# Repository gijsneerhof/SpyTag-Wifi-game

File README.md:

# WIFI Spy Tag game

Hey there, this is the code used for the WIFI based hide and seek/tag game using ESP8266 devices.
The idea behind the game is that humans go and hide, while two zombies (or agents) start seeking them out.
once a zombie comes in proximity to a human, they turn into zombies themselves. Eventually this game will
be rebranded to a spy type of game, with more powerups and features to play around with.

This project is currently in basic WIP shape, if you would like to burn and test out this project however,
more info can be found here for how to accomplish this: https://github.com/con-f-use/esp82XX-basic

## Hardware

Coming soon!

## Instructions

### Installation

Espressif IDF toolchain

### Usage

The function `user_init()` in `user/user_main.c` will be run first. 

### Building

First do `make erase`, then `make initdefault #init3v3` to set the flash correctly.
Lastly, use `make burn` to upload to the ESP8266 controller over `/dev/ttyUSB0`

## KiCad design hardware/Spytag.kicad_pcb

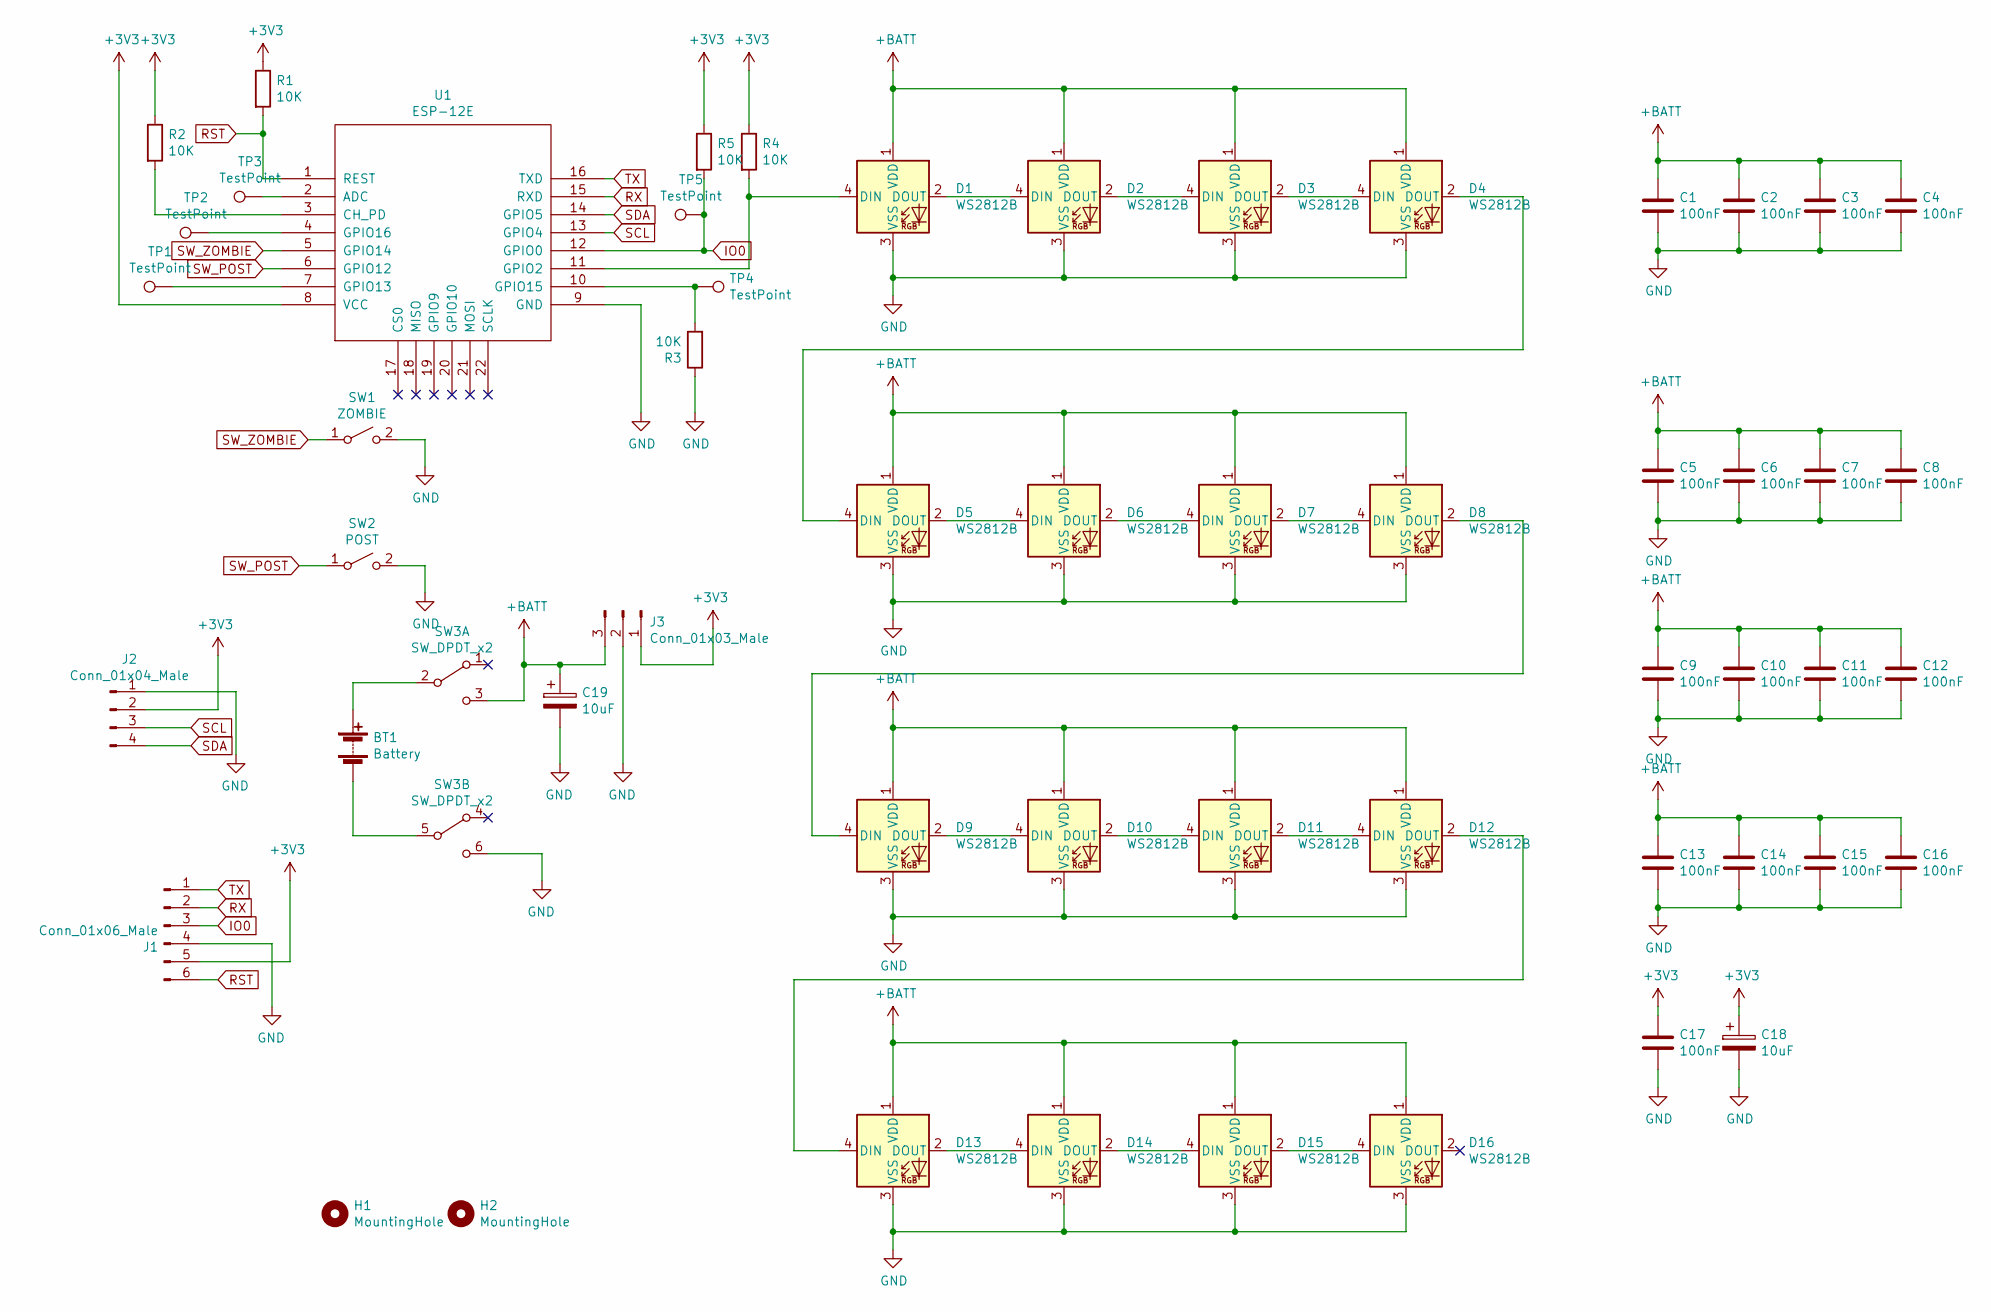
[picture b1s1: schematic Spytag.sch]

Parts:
BT1: Battery; Generic
C1, C2, C3, C4, C5, C6, C7, C8, C9, C10, C11, C12, C13, C14, C15, C16, C17: 100nF; C_0603_1608Metric
C18, C19: 10uF; C_0603_1608Metric
D1, D2, D3, D4, D5, D6, D7, D8, D9, D10, D11, D12, D13, D14, D15, D16: WS2812B; LED_WS2812B_PLCC4_5.0x5.0mm_P3.2mm
H1, H2: MountingHole; MountingHole_3.2mm_M3
J1: Conn_01x06_Male; PinHeader_1x06_P2.54mm_Vertical
J2: Conn_01x04_Male; PinHeader_1x04_P2.54mm_Vertical
J3: Conn_01x03_Male; PinSocket_1x03_P2.54mm_Vertical
R1, R2, R3, R4, R5: 10K; R_0603_1608Metric
SW1: ZOMBIE; SW_PUSH_6mm
SW2: POST; SW_PUSH_6mm
SW3: SW_DPDT_x2; SW_E-Switch_EG1271_DPDT
TP1, TP2, TP3, TP4, TP5: TestPoint; TestPoint_THTPad_D1.5mm_Drill0.7mm
U1: ESP-12E; ESP-12E_SMD

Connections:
+3V3: C17.1, C18.1, J1.5, J2.2, J3.1, R1.1, R2.1, R4.1, R5.1, U1.8 (VCC)
+BATT: C1.1, C2.1, C3.1, C4.1, C5.1, C6.1, C7.1, C8.1, C9.1, C10.1, C11.1, C12.1, C13.1, C14.1, C15.1, C16.1, C19.1, D1.1 (VDD), D2.1 (VDD), D3.1 (VDD), D4.1 (VDD), D5.1 (VDD), D6.1 (VDD), D7.1 (VDD), D8.1 (VDD), D9.1 (VDD), D10.1 (VDD), D11.1 (VDD), D12.1 (VDD), D13.1 (VDD), D14.1 (VDD), D15.1 (VDD), D16.1 (VDD), J3.3, SW3.3 (C)
GND: C1.2, C2.2, C3.2, C4.2, C5.2, C6.2, C7.2, C8.2, C9.2, C10.2, C11.2, C12.2, C13.2, C14.2, C15.2, C16.2, C17.2, C18.2, C19.2, D1.3 (VSS), D2.3 (VSS), D3.3 (VSS), D4.3 (VSS), D5.3 (VSS), D6.3 (VSS), D7.3 (VSS), D8.3 (VSS), D9.3 (VSS), D10.3 (VSS), D11.3 (VSS), D12.3 (VSS), D13.3 (VSS), D14.3 (VSS), D15.3 (VSS), D16.3 (VSS), J1.4, J2.1, J3.2, R3.1, SW1.2 (B), SW2.2 (B), SW3.6 (C), U1.9 (GND)
IO0: J1.3, R5.2, TP5.1, U1.12 (GPIO0)
unnamed: BT1.1 (+), SW3.2 (B)
unnamed: BT1.2 (-), SW3.5 (B)
unnamed: D1.2 (DOUT), D2.4 (DIN)
unnamed: D1.4 (DIN), R4.2, U1.11 (GPIO2)
unnamed: D2.2 (DOUT), D3.4 (DIN)
unnamed: D3.2 (DOUT), D4.4 (DIN)
unnamed: D4.2 (DOUT), D5.4 (DIN)
unnamed: D5.2 (DOUT), D6.4 (DIN)
unnamed: D6.2 (DOUT), D7.4 (DIN)
unnamed: D7.2 (DOUT), D8.4 (DIN)
unnamed: D8.2 (DOUT), D9.4 (DIN)
unnamed: D10.2 (DOUT), D11.4 (DIN)
unnamed: D9.2 (DOUT), D10.4 (DIN)
unnamed: D11.2 (DOUT), D12.4 (DIN)
unnamed: D12.2 (DOUT), D13.4 (DIN)
unnamed: D13.2 (DOUT), D14.4 (DIN)
unnamed: D14.2 (DOUT), D15.4 (DIN)
unnamed: D15.2 (DOUT), D16.4 (DIN)
unnamed: R2.2, U1.3 (CH_PD)
unnamed: R3.2, TP4.1, U1.10 (GPIO15)
unnamed: TP1.1, U1.7 (GPIO13)
unnamed: TP2.1, U1.4 (GPIO16)
unnamed: TP3.1, U1.2 (ADC)
RST: J1.6, R1.2, U1.1 (REST)
RX: J1.2, U1.15 (RXD)
SCL: J2.3, U1.13 (GPIO4)
SDA: J2.4, U1.14 (GPIO5)
SW_POST: SW2.1 (A), U1.6 (GPIO12)
SW_ZOMBIE: SW1.1 (A), U1.5 (GPIO14)
TX: J1.1, U1.16 (TXD)

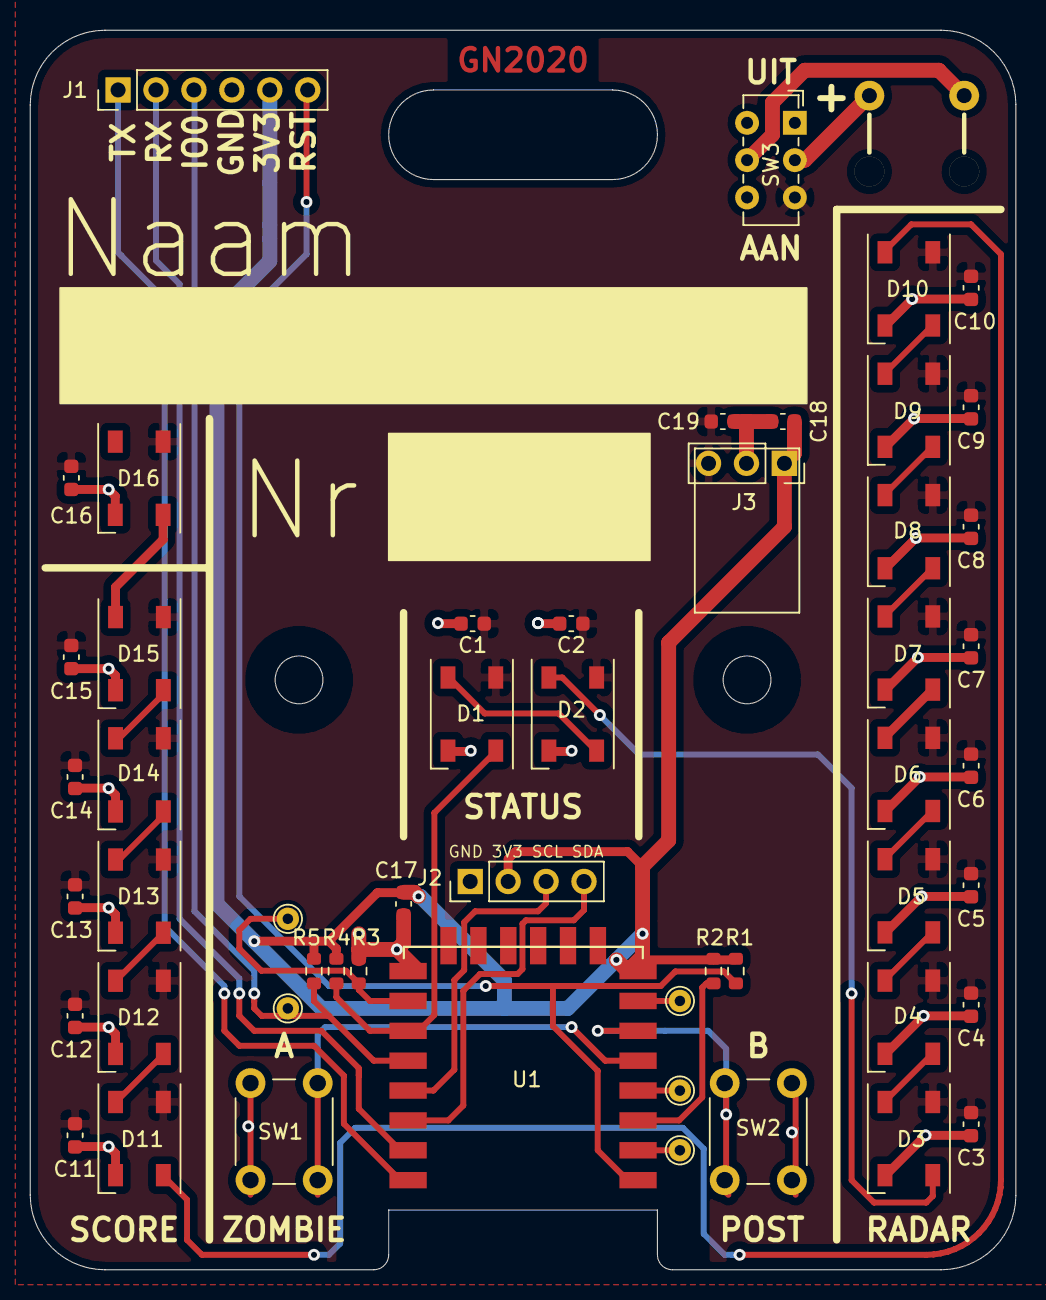
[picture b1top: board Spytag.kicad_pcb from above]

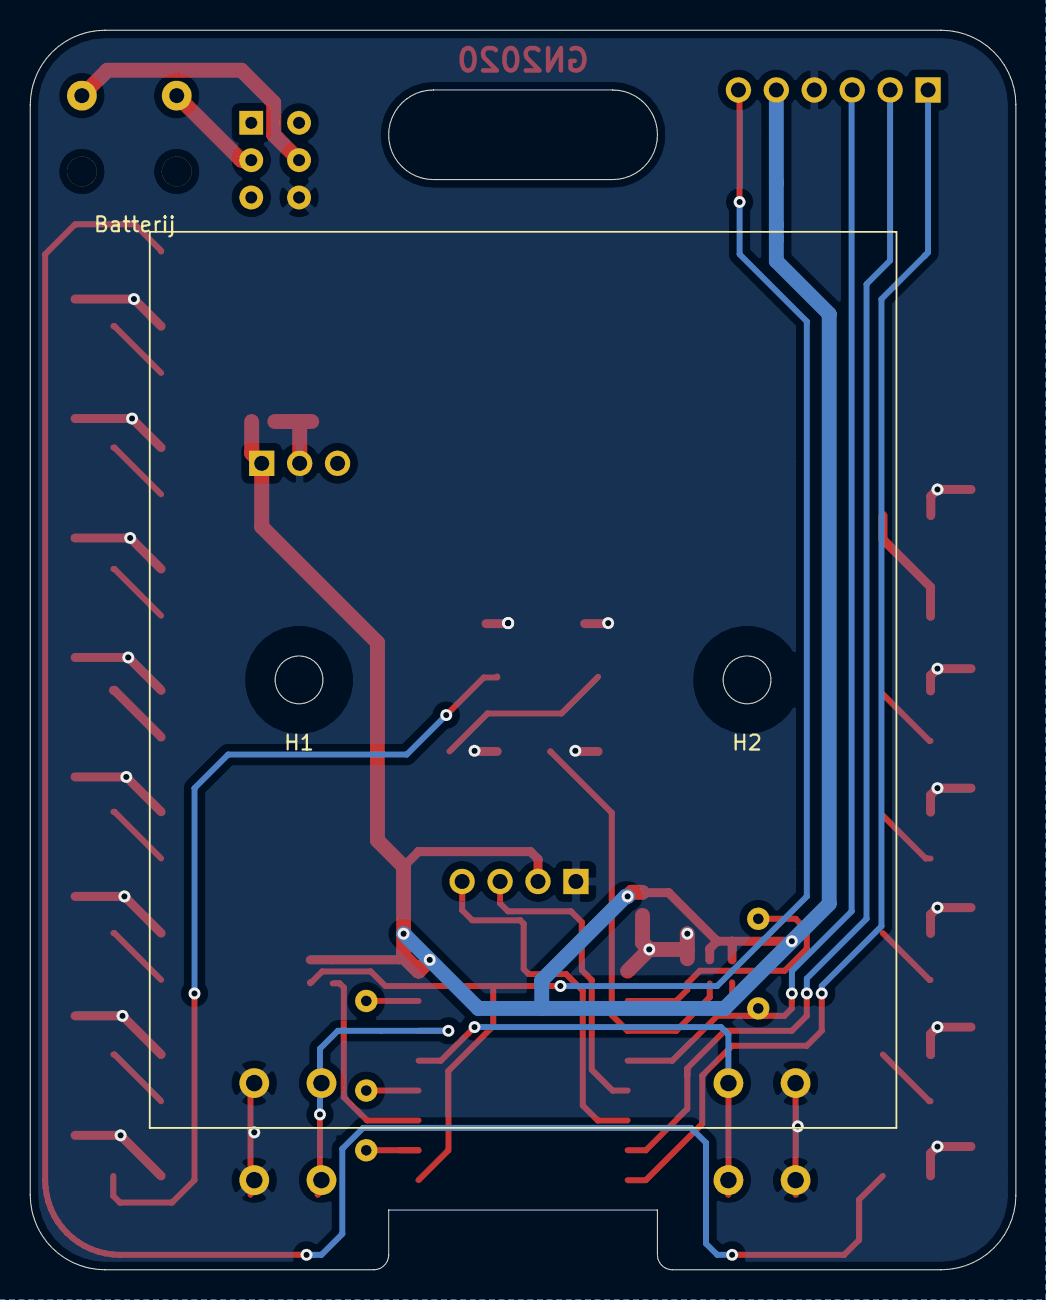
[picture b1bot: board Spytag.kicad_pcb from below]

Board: 2 copper layers, 66.0 x 83.0 mm, 55 parts (2 on the bottom side), 34 nets.

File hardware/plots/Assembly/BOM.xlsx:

|  |  | Designator | Comment | Footprint
 |  |  | C1, C2, C3, C4, C5, C6, C7, C8, C9, C10, C11, C12, C13, C14, C15, C16, C17 | 100nF | C_0603_1608Metric
 |  |  | C18, C19 | 10uF | C_0603_1608Metric
 |  |  | R1, R2, R3, R4, R5 | 10K | R_0603_1608Metric
 |  |  | D1, D2, D3, D4, D5, D6, D7, D8, D9, D10, D11, D12, D13, D14, D15, D16 | WS2812B | LED_WS2812B_PLCC4_5.0x5.0mm_P3.2mm
 |  |  | U1 | ESP-12E | ESP-12E_SMD
 |  |  | SW3 | SW_DPDT_x2 | SW_E-Switch_EG1271_DPDT
 |  |  | SW1 | ZOMBIE | SW_PUSH_6mm

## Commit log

2020-09-06 removed not working submodule
2020-09-06 added submodule
2020-09-06 Update esp82xx
    updated commit
2020-09-06 chaged makefile structure
2020-09-06 changed LED code
2020-09-06 commented not working code
2020-09-06 Added printline
2020-09-06 reformat document
2020-09-06 changed variable type
2020-09-06 changed unkown characters
2020-09-06 changed allocation
2020-09-06 changed typo
2020-09-06 more typos
2020-09-06 make begin game timer working
2020-09-07 removed all blob code
2020-09-07 changed LED workings and made them brighter
2020-09-07 added comments, change state on BButotn to zombie
2020-09-07 fixed grace period LED
2020-09-08 removed brightness edit
2020-09-08 Update user_main.c
    added comment
2020-09-08 updated LEDs on init
2020-09-08 changed Init order
2020-09-08 fixed type
2020-09-08 fixed
2020-09-08 added make options
2020-09-08 Revert "added make options"
    This reverts commit 09e14efeac307edcb212265a1da913de265295c1.
2020-09-23 decreased grace period time added color switch in grace period (zombie /human)
2020-09-23 fixed mistake
2020-09-27 made mentioned changes added score ability
2020-09-27 added noteam option back in
2020-09-27 fixed typos
2020-09-27 last typo fixed
2020-09-27 fix to radar
2020-09-27 changes to radarr
2020-09-27 fix to radar balance
2020-09-27 final changes
2020-09-27 still on radar
2020-09-27 removed printing
2020-09-27 rebuild make radar
2020-09-27 better radar?
2020-09-27 dunno
2020-09-27 does this work?
2020-09-27 do this
2020-09-27 more
2020-09-27 changed sensitivity and radar
2020-10-05 Update user_main.c
    made noteam better
2020-10-05 Update gpio_buttons.c
    change button a
2020-10-05 Revert "Update gpio_buttons.c"
    This reverts commit 5f7945b347dd6e14e88b455876220a88865fb2e6.
2020-10-05 Revert "Update gpio_buttons.c"
    This reverts commit a8e8c395f52333198364e11942960c95ad1f11ff.
2020-10-05 Update user_main.c
    changed butto nvalues
2020-10-07 Update user_main.c
    show score on endgame
2020-10-14 Update user_main.c
    included endgame, changed radar, add
2020-10-15 Update user_main.c
    fixed
2020-10-15 Update gpio_buttons.c
    changed buttons to check
2020-10-15 Update gpio_buttons.c
    fixed typos
2020-10-15 Revert "Update gpio_buttons.c"
    This reverts commit e5e5ab5289cdb038afbc0b2c327998b03ec83b32.
2020-10-15 Revert "Update gpio_buttons.c"
    This reverts commit 4178669b4f6e888c402663ea6bbbc4730a29600e.
2020-10-15 Revert "Update gpio_buttons.c"
    This reverts commit 261d45f54d4ae01195b26ec9ca1ff1db794dddcb.
2020-10-15 Revert "Update gpio_buttons.c"
    This reverts commit 855671d98141f3110729214135b2724edba1bcfd.
2020-10-29 added kicad design
